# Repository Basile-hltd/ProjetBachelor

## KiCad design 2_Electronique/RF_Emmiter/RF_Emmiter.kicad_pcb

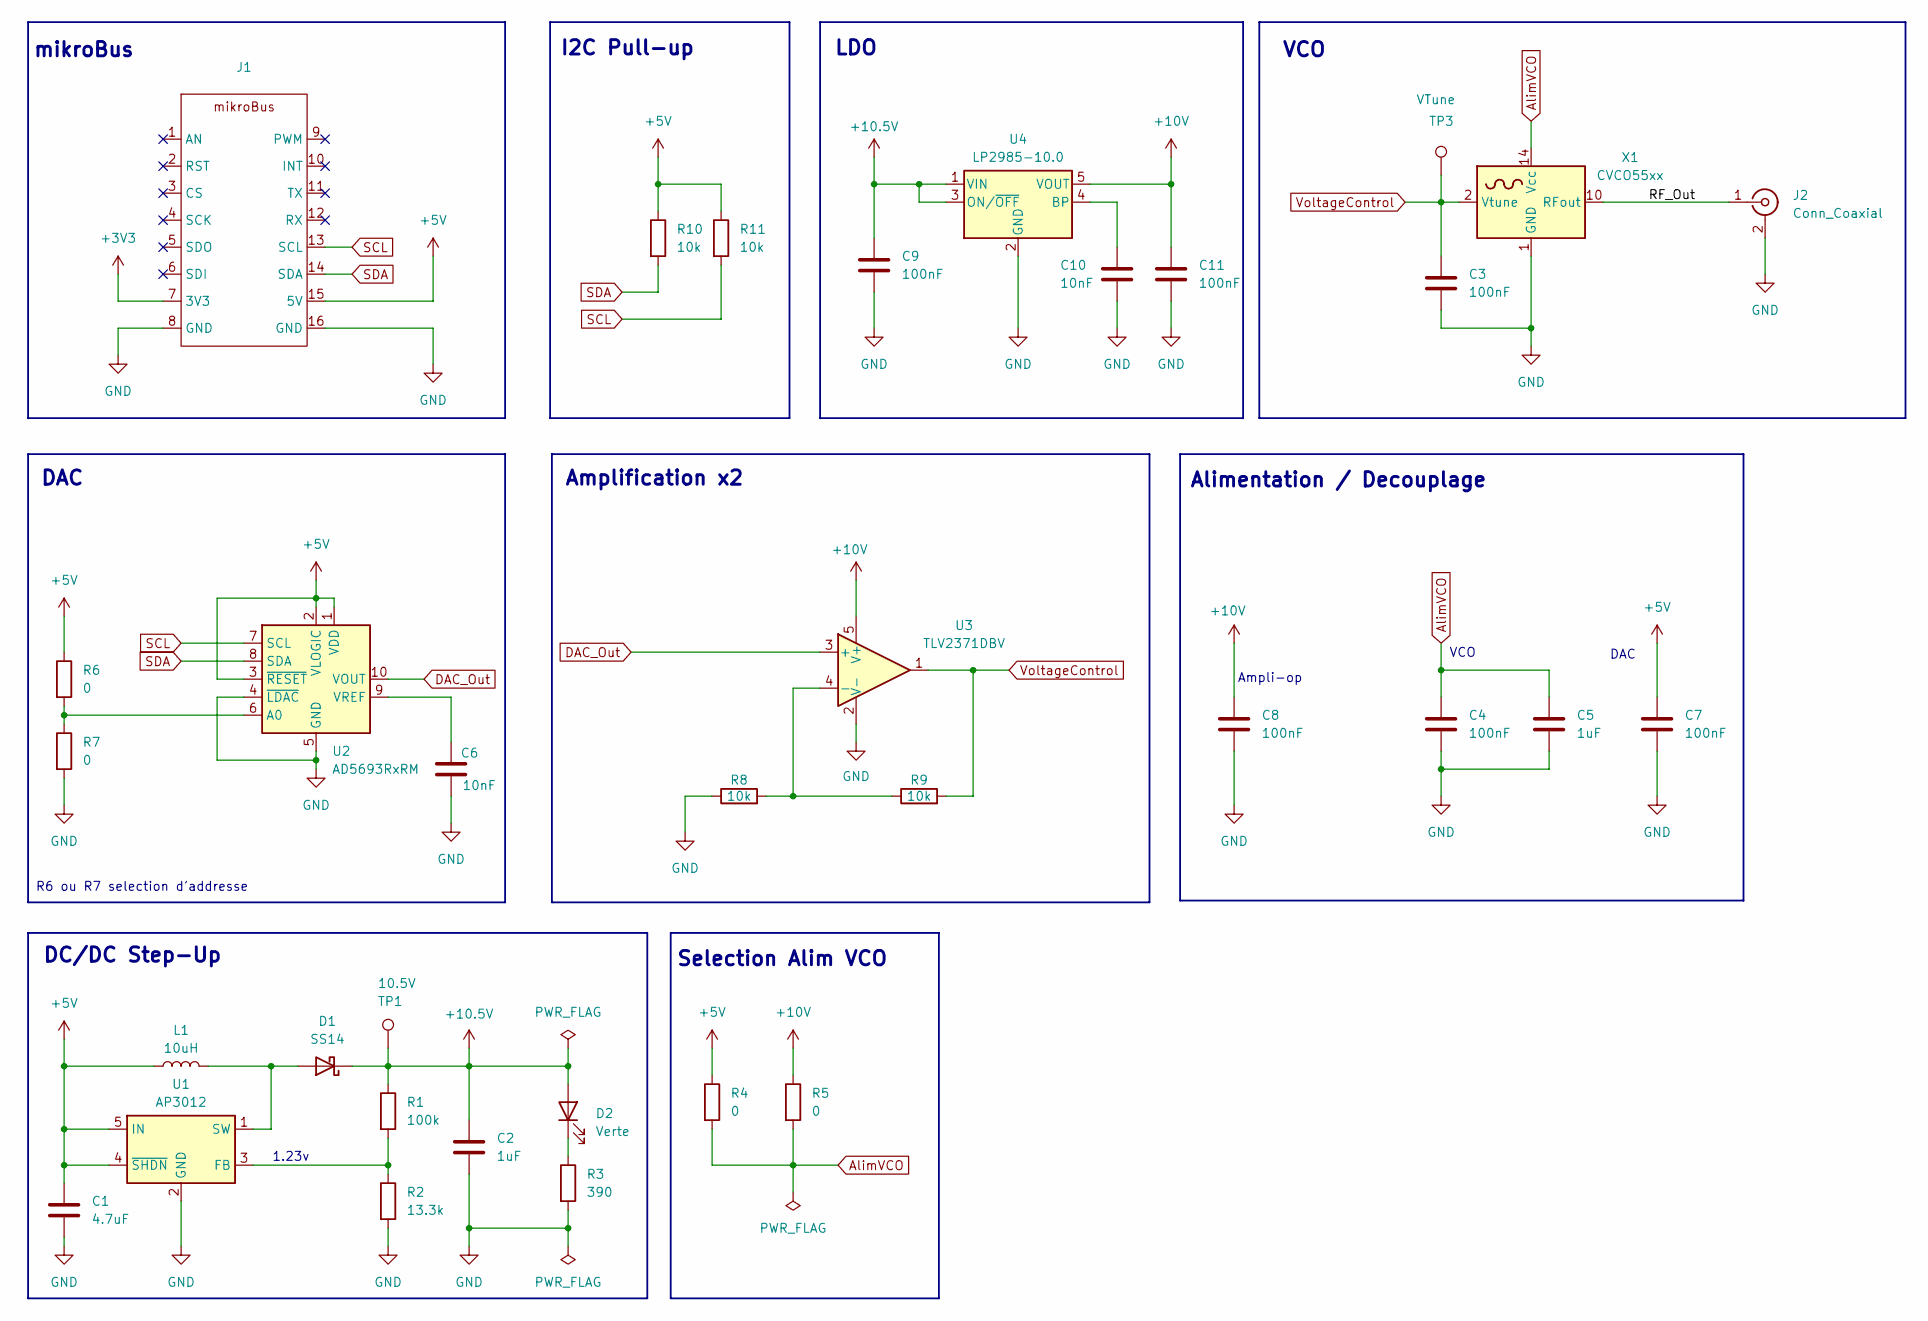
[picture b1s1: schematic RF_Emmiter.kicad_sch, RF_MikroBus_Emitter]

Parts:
C1: 4.7uF; C_0805_2012Metric_Pad1.18x1.45mm_HandSolder
C2, C5: 1uF; C_0805_2012Metric_Pad1.18x1.45mm_HandSolder
C3, C4, C7, C8, C9, C11: 100nF; C_0805_2012Metric_Pad1.18x1.45mm_HandSolder
C6, C10: 10nF; C_0805_2012Metric_Pad1.18x1.45mm_HandSolder
D1: SS14; D_SMA_Handsoldering
D2: Verte; LED_0805_2012Metric_Pad1.15x1.40mm_HandSolder
J1: mikroBus
J2: Conn_Coaxial; SMA_Samtec_SMA-J-P-H-ST-EM1_EdgeMount
L1: 10uH; L_0805_2012Metric_Pad1.15x1.40mm_HandSolder
R1: 100k; R_0805_2012Metric_Pad1.20x1.40mm_HandSolder
R2: 13.3k; R_0805_2012Metric_Pad1.20x1.40mm_HandSolder
R3: 390; R_0805_2012Metric_Pad1.20x1.40mm_HandSolder
R4, R5, R6, R7: 0; R_0805_2012Metric_Pad1.20x1.40mm_HandSolder
R8, R9, R10, R11: 10k; R_0805_2012Metric_Pad1.20x1.40mm_HandSolder
TP1: 10.5V; TestPoint_Pad_D1.5mm
TP3: VTune; TestPoint_Pad_D1.5mm
U1: AP3012; SOT-23-5
U2: AD5693RxRM; MSOP-10_3x3mm_P0.5mm
U3: TLV2371DBV; SOT-23-5
U4: LP2985-10.0; SOT-23-5
X1: CVCO55xx; Mini-Circuits_CK605_LandPatternPL-012

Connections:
+3V3: J1.7 (3V3)
+5V: C1.1, C7.1, J1.15 (5V), L1.1, R4.1, R6.1, R10.1, R11.1, U1.4 (~SHDN), U1.5 (IN), U2.1 (VDD), U2.2 (VLOGIC), U2.3 (~RESET)
+10.5V: C2.1, C9.1, D1.1 (K), D2.2 (A), R1.1, TP1.1, U4.1 (VIN), U4.3 (ON/~OFF)
+10V: C8.1, C11.1, R5.1, U3.5 (V+), U4.5 (VOUT)
/RF_Out: J2.1 (In), X1.10 (RFout)
AlimVCO: C4.1, C5.1, R4.2, R5.2, X1.14 (Vcc)
DAC_Out: U2.10 (VOUT), U3.3 (+)
GND: C1.2, C2.2, C3.2, C4.2, C5.2, C6.2, C7.2, C8.2, C9.2, C10.2, C11.2, J1.8 (GND), J1.16 (GND), J2.2 (Ext), R2.2, R3.2, R7.2, R8.1, U1.2 (GND), U2.4 (~LDAC), U2.5 (GND), U3.2 (V-), U4.2 (GND), X1.1 (GND), X1.3 (GND), X1.4 (GND), X1.5 (GND), X1.6 (GND), X1.7 (GND), X1.8 (GND), X1.9 (GND), X1.11 (GND), X1.12 (GND), X1.13 (GND), X1.15 (GND), X1.16 (GND)
unnamed: D1.2 (A), L1.2, U1.1 (SW)
unnamed: D2.1 (K), R3.1
unnamed: R1.2, R2.1, U1.3 (FB)
unnamed: R6.2, R7.1, U2.6 (A0)
unnamed: C6.1, U2.9 (VREF)
unnamed: R8.2, R9.1, U3.4 (-)
unnamed: C10.1, U4.4 (BP)
SCL: J1.13 (SCL), R11.2, U2.7 (SCL)
SDA: J1.14 (SDA), R10.2, U2.8 (SDA)
VoltageControl: C3.1, R9.2, TP3.1, U3.1, X1.2 (Vtune)

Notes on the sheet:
LDO
mikroBus
1.23v
DAC
VCO
R6 ou R7 selection d'addresse
DC/DC Step-Up
I2C Pull-up
Alimentation / Decouplage
VCO
Ampli-op
Selection Alim VCO
Amplification x2

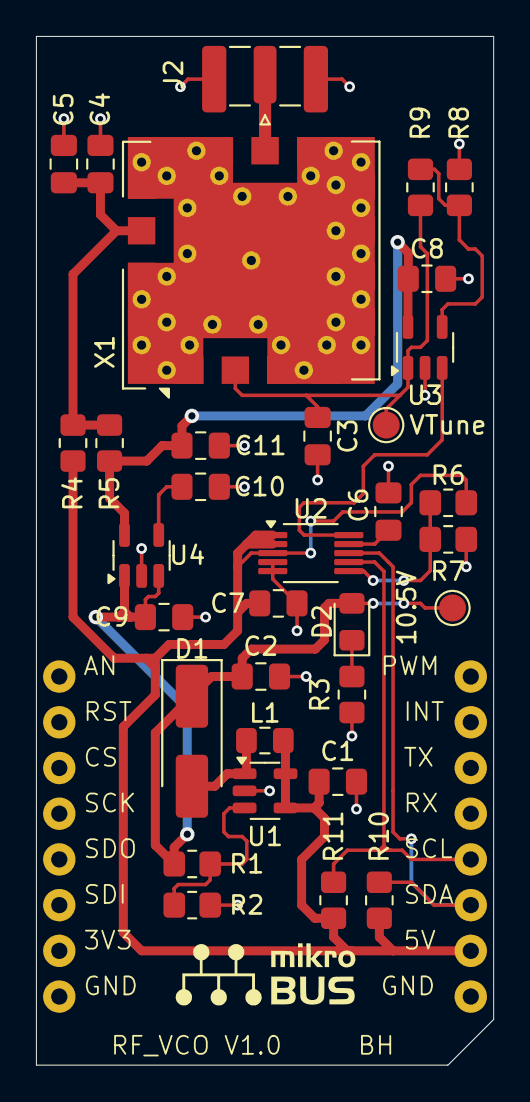
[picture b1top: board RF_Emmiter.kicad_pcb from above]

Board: 2 copper layers, 25.4 x 57.1 mm, 34 parts (0 on the bottom side), 17 nets.

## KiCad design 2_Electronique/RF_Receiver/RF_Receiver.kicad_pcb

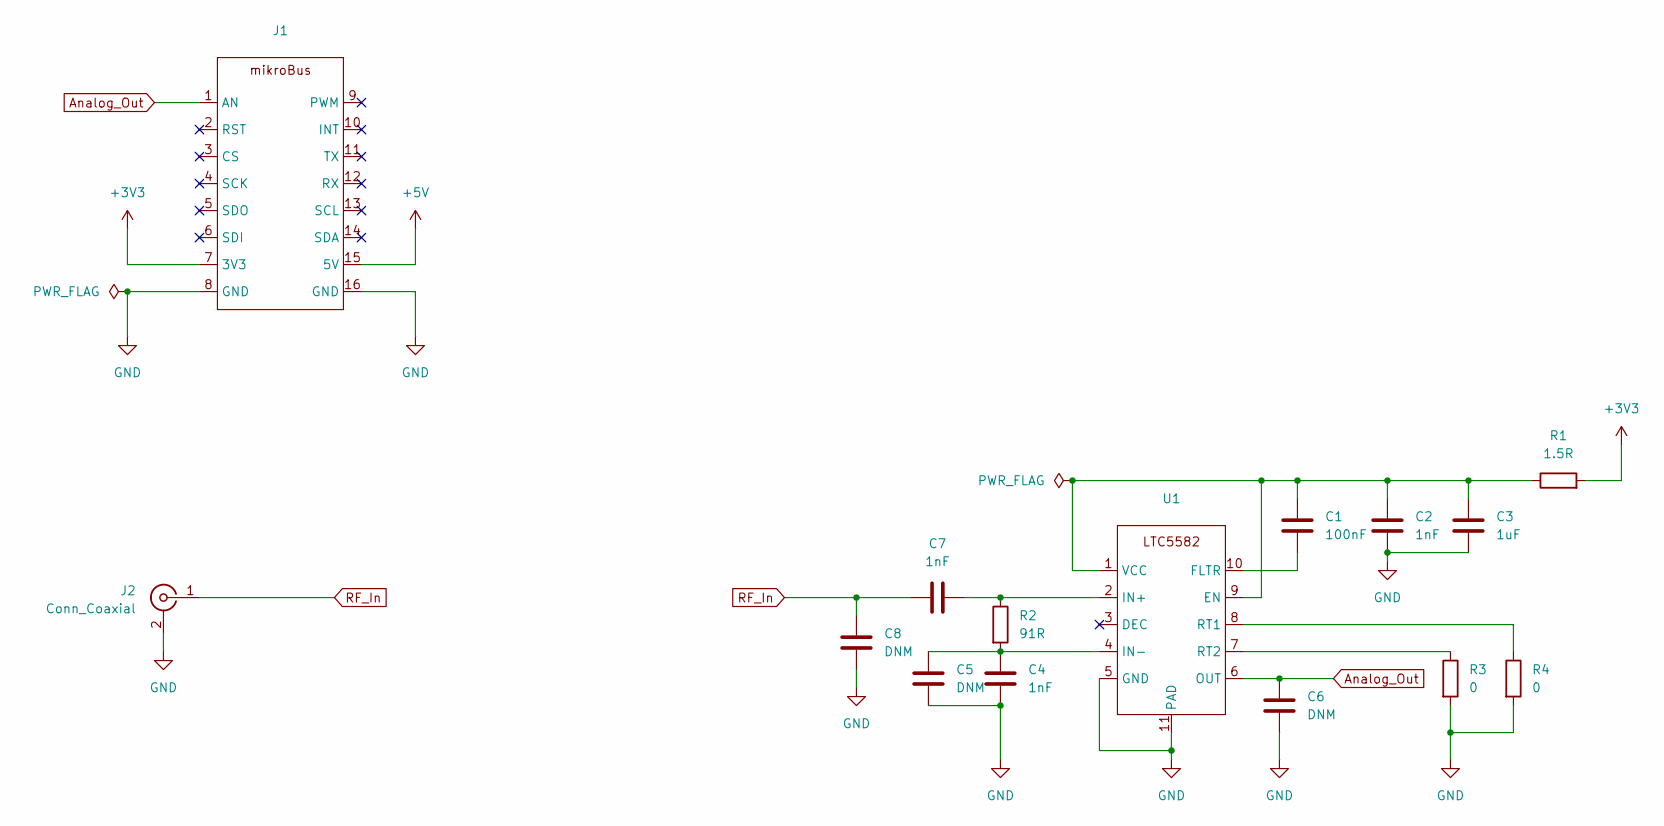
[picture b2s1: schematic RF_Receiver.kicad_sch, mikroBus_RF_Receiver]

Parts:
C1: 100nF; C_0805_2012Metric_Pad1.18x1.45mm_HandSolder
C2, C4, C7: 1nF; C_0805_2012Metric_Pad1.18x1.45mm_HandSolder
C3: 1uF; C_0805_2012Metric_Pad1.18x1.45mm_HandSolder
C5, C6, C8: DNM; C_0805_2012Metric_Pad1.18x1.45mm_HandSolder
J1: mikroBus
J2: Conn_Coaxial; SMA_Samtec_SMA-J-P-H-ST-EM1_EdgeMount
R1: 1.5R; R_0805_2012Metric_Pad1.20x1.40mm_HandSolder
R2: 91R; R_0603_1608Metric_Pad0.98x0.95mm_HandSolder
R3, R4: 0; R_0805_2012Metric_Pad1.20x1.40mm_HandSolder
U1: DFN-10-1EP_3x3mm_P0.5mm_EP1.7x2.5mm

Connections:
+3V3: J1.7 (3V3), R1.2
+5V: J1.15 (5V)
Analog_Out: C6.1, J1.1 (AN), U1.6 (OUT)
GND: C2.2, C3.2, C4.2, C5.2, C6.2, C8.1, J1.8 (GND), J1.16 (GND), J2.2 (Ext), R3.2, R4.2, U1.5 (GND), U1.11 (PAD)
unnamed: C1.1, C2.1, C3.1, R1.1, U1.1 (VCC), U1.9 (EN)
unnamed: C1.2, U1.10 (FLTR)
unnamed: C7.2, R2.1, U1.2 (IN+)
unnamed: C4.1, C5.1, R2.2, U1.4 (IN-)
unnamed: R4.1, U1.8 (RT1)
unnamed: R3.1, U1.7 (RT2)
RF_In: C7.1, C8.2, J2.1 (In)

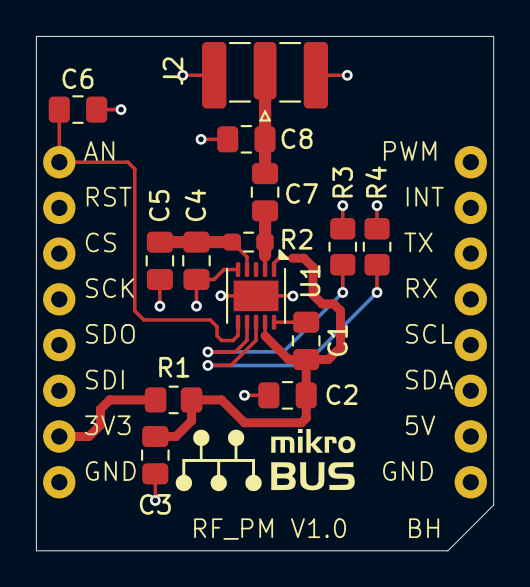
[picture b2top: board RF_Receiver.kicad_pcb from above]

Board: 2 copper layers, 25.4 x 28.6 mm, 15 parts (0 on the bottom side), 10 nets.

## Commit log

2025-04-29 Ajout affiche et présentation
    Premier commit
2025-04-29 Rename Presentation Bachelor.pptx to Diapo Bachelor.pptx
2025-04-29 Ajout de fichiers
2025-04-29 Rename file
2025-05-05 Mesures stub microruban
2025-05-06 ajout mesure CPW Stub
2025-05-16 Ajout des mesures du CPW a 2.5Ghz
2025-05-26 Ajout doc dspic et microbus et carte de dev
2025-05-27 Ajout doc compilateur et ide
2025-05-27 Ajout main.py
2025-05-27 Ajout connection usb en finir
2025-05-27 add first c file
2025-05-27 codage connection usb
2025-05-27 Config led RGB
2025-05-28 Creation projet C ajout message de validation de connexion sur l'uart
2025-05-28 Ajout dashboard et menu
2025-05-30 ajout timer pour tetection deconection
2025-05-30 ajoue adc
2025-05-30 modif serial
2025-06-02 Ajout mesure adc
2025-06-02 ajout mesure et envoie adc modif protocol uart
2025-06-10 ajout rapport expert
2025-07-01 ajout cours propagation ferrari
2026-04-14 Ajout rapport finale
2026-04-30 Merci Guillaume pour cette clef usb
